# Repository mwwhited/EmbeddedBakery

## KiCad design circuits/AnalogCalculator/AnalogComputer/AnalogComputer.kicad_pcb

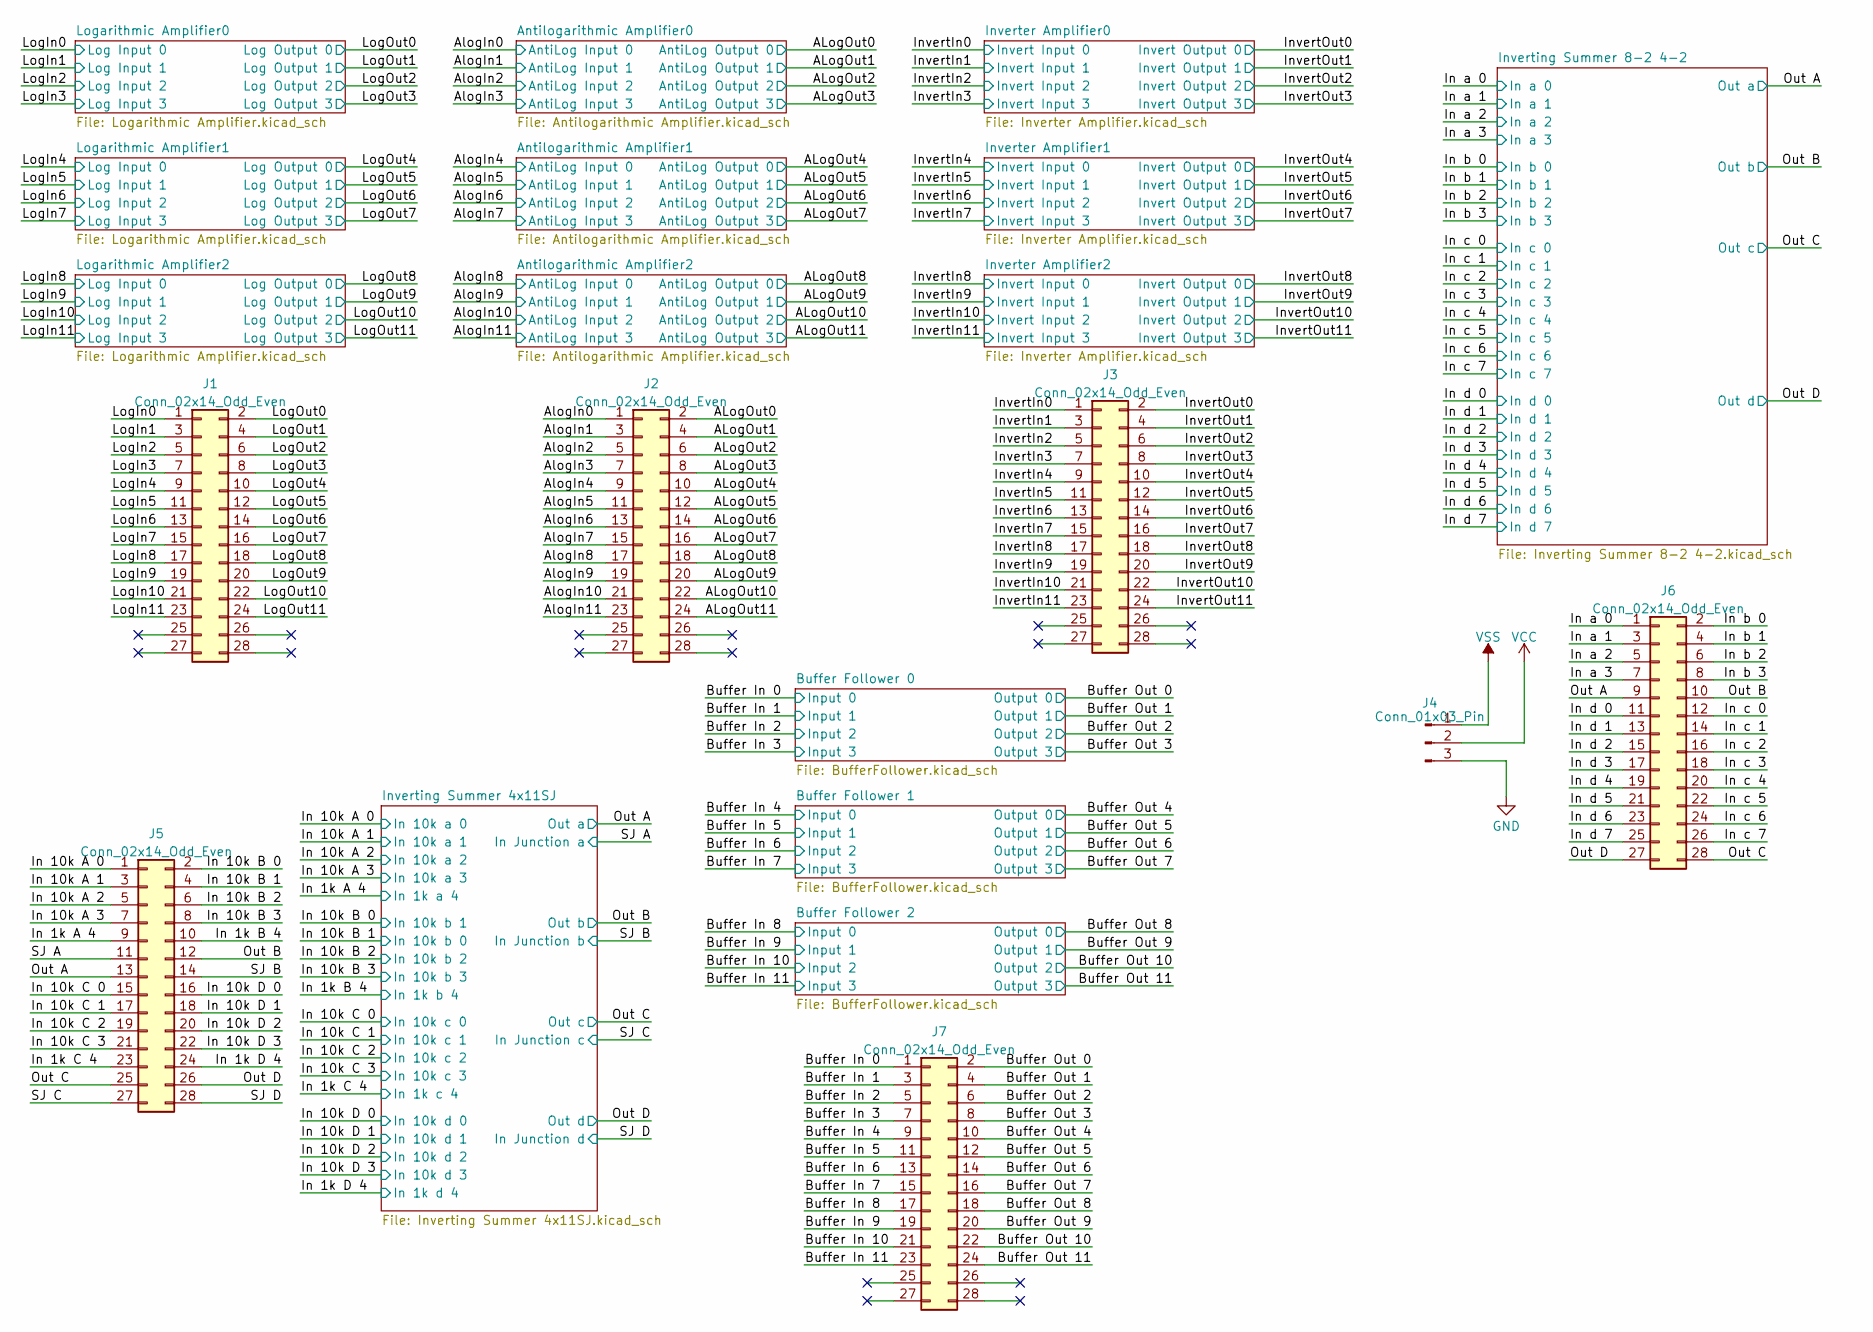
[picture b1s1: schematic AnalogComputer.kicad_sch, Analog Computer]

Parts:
J1, J2, J3, J5, J6, J7: Conn_02x14_Odd_Even; PinHeader_2x14_P2.54mm_Vertical
J4: Conn_01x03_Pin; JST_XH_B3B-XH-AM_1x03_P2.50mm_Vertical

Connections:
/ALogOut0: J2.2; also elsewhere on the board
/ALogOut1: J2.4; also elsewhere on the board
/ALogOut2: J2.6; also elsewhere on the board
/ALogOut3: J2.8; also elsewhere on the board
/ALogOut4: J2.10; also elsewhere on the board
/ALogOut5: J2.12; also elsewhere on the board
/ALogOut6: J2.14; also elsewhere on the board
/ALogOut7: J2.16; also elsewhere on the board
/ALogOut8: J2.18; also elsewhere on the board
/ALogOut9: J2.20; also elsewhere on the board
/ALogOut10: J2.22; also elsewhere on the board
/ALogOut11: J2.24; also elsewhere on the board
/AlogIn0: J2.1; also elsewhere on the board
/AlogIn1: J2.3; also elsewhere on the board
/AlogIn2: J2.5; also elsewhere on the board
/AlogIn3: J2.7; also elsewhere on the board
/AlogIn4: J2.9; also elsewhere on the board
/AlogIn5: J2.11; also elsewhere on the board
/AlogIn6: J2.13; also elsewhere on the board
/AlogIn7: J2.15; also elsewhere on the board
/AlogIn8: J2.17; also elsewhere on the board
/AlogIn9: J2.19; also elsewhere on the board
/AlogIn10: J2.21; also elsewhere on the board
/AlogIn11: J2.23; also elsewhere on the board
/Buffer In 0: J7.1; also elsewhere on the board
/Buffer In 1: J7.3; also elsewhere on the board
/Buffer In 2: J7.5; also elsewhere on the board
/Buffer In 3: J7.7; also elsewhere on the board
/Buffer In 4: J7.9; also elsewhere on the board
/Buffer In 5: J7.11; also elsewhere on the board
/Buffer In 6: J7.13; also elsewhere on the board
/Buffer In 7: J7.15; also elsewhere on the board
/Buffer In 8: J7.17; also elsewhere on the board
/Buffer In 9: J7.19; also elsewhere on the board
/Buffer In 10: J7.21; also elsewhere on the board
/Buffer In 11: J7.23; also elsewhere on the board
/Buffer Out 0: J7.2; also elsewhere on the board
/Buffer Out 1: J7.4; also elsewhere on the board
/Buffer Out 2: J7.6; also elsewhere on the board
/Buffer Out 3: J7.8; also elsewhere on the board
/Buffer Out 4: J7.10; also elsewhere on the board
/Buffer Out 5: J7.12; also elsewhere on the board
/Buffer Out 6: J7.14; also elsewhere on the board
/Buffer Out 7: J7.16; also elsewhere on the board
/Buffer Out 8: J7.18; also elsewhere on the board
/Buffer Out 9: J7.20; also elsewhere on the board
/Buffer Out 10: J7.22; also elsewhere on the board
/Buffer Out 11: J7.24; also elsewhere on the board
/In 1k A 4: J5.9; also elsewhere on the board
/In 1k B 4: J5.10; also elsewhere on the board
/In 1k C 4: J5.23; also elsewhere on the board
/In 1k D 4: J5.24; also elsewhere on the board
/In 10k A 0: J5.1; also elsewhere on the board
/In 10k A 1: J5.3; also elsewhere on the board
/In 10k A 2: J5.5; also elsewhere on the board
/In 10k A 3: J5.7; also elsewhere on the board
/In 10k B 0: J5.2; also elsewhere on the board
/In 10k B 1: J5.4; also elsewhere on the board
/In 10k B 2: J5.6; also elsewhere on the board
/In 10k B 3: J5.8; also elsewhere on the board
/In 10k C 0: J5.15; also elsewhere on the board
/In 10k C 1: J5.17; also elsewhere on the board
/In 10k C 2: J5.19; also elsewhere on the board
/In 10k C 3: J5.21; also elsewhere on the board
/In 10k D 0: J5.16; also elsewhere on the board
/In 10k D 1: J5.18; also elsewhere on the board
/In 10k D 2: J5.20; also elsewhere on the board
/In 10k D 3: J5.22; also elsewhere on the board
/In a 0: J6.1; also elsewhere on the board
/In a 1: J6.3; also elsewhere on the board
/In a 2: J6.5; also elsewhere on the board
/In a 3: J6.7; also elsewhere on the board
/In b 0: J6.2; also elsewhere on the board
/In b 1: J6.4; also elsewhere on the board
/In b 2: J6.6; also elsewhere on the board
/In b 3: J6.8; also elsewhere on the board
/In c 0: J6.12; also elsewhere on the board
/In c 1: J6.14; also elsewhere on the board
/In c 2: J6.16; also elsewhere on the board
/In c 3: J6.18; also elsewhere on the board
/In c 4: J6.20; also elsewhere on the board
/In c 5: J6.22; also elsewhere on the board
/In c 6: J6.24; also elsewhere on the board
/In c 7: J6.26; also elsewhere on the board
/In d 0: J6.11; also elsewhere on the board
/In d 1: J6.13; also elsewhere on the board
/In d 2: J6.15; also elsewhere on the board
/In d 3: J6.17; also elsewhere on the board
/In d 4: J6.19; also elsewhere on the board
/In d 5: J6.21; also elsewhere on the board
/In d 6: J6.23; also elsewhere on the board
/In d 7: J6.25; also elsewhere on the board
/InvertIn0: J3.1; also elsewhere on the board
/InvertIn1: J3.3; also elsewhere on the board
/InvertIn2: J3.5; also elsewhere on the board
/InvertIn3: J3.7; also elsewhere on the board
/InvertIn4: J3.9; also elsewhere on the board
/InvertIn5: J3.11; also elsewhere on the board
/InvertIn6: J3.13; also elsewhere on the board
/InvertIn7: J3.15; also elsewhere on the board
/InvertIn8: J3.17; also elsewhere on the board
/InvertIn9: J3.19; also elsewhere on the board
/InvertIn10: J3.21; also elsewhere on the board
/InvertIn11: J3.23; also elsewhere on the board
/InvertOut4: J3.10; also elsewhere on the board
/InvertOut5: J3.12; also elsewhere on the board
/InvertOut6: J3.14; also elsewhere on the board
/InvertOut7: J3.16; also elsewhere on the board
/InvertOut8: J3.18; also elsewhere on the board
/InvertOut9: J3.20; also elsewhere on the board
/InvertOut10: J3.22; also elsewhere on the board
/InvertOut11: J3.24; also elsewhere on the board
/LogIn0: J1.1; also elsewhere on the board
/LogIn1: J1.3; also elsewhere on the board
/LogIn2: J1.5; also elsewhere on the board
/LogIn3: J1.7; also elsewhere on the board
/LogIn4: J1.9; also elsewhere on the board
/LogIn5: J1.11; also elsewhere on the board
/LogIn6: J1.13; also elsewhere on the board
/LogIn7: J1.15; also elsewhere on the board
/LogIn8: J1.17; also elsewhere on the board
/LogIn9: J1.19; also elsewhere on the board
/LogIn10: J1.21; also elsewhere on the board
/LogIn11: J1.23; also elsewhere on the board
/LogOut0: J1.2; also elsewhere on the board
/LogOut1: J1.4; also elsewhere on the board
/LogOut2: J1.6; also elsewhere on the board
/LogOut3: J1.8; also elsewhere on the board
/LogOut4: J1.10; also elsewhere on the board
/LogOut5: J1.12; also elsewhere on the board
/LogOut6: J1.14; also elsewhere on the board
/LogOut7: J1.16; also elsewhere on the board
/LogOut8: J1.18; also elsewhere on the board
/LogOut9: J1.20; also elsewhere on the board
/LogOut10: J1.22; also elsewhere on the board
/LogOut11: J1.24; also elsewhere on the board
/Out A: J6.9; also elsewhere on the board
/Out B: J6.10; also elsewhere on the board
/Out C: J6.28; also elsewhere on the board
/Out D: J6.27; also elsewhere on the board
/Out A: J5.13; also elsewhere on the board
/Out B: J5.12; also elsewhere on the board
/Out C: J5.25; also elsewhere on the board
/Out D: J5.26; also elsewhere on the board
/SJ A: J5.11; also elsewhere on the board
/SJ B: J5.14; also elsewhere on the board
/SJ C: J5.27; also elsewhere on the board
/SJ D: J5.28; also elsewhere on the board
GND: J4.3; also elsewhere on the board
VCC: J4.2; also elsewhere on the board
VSS: J4.1; also elsewhere on the board

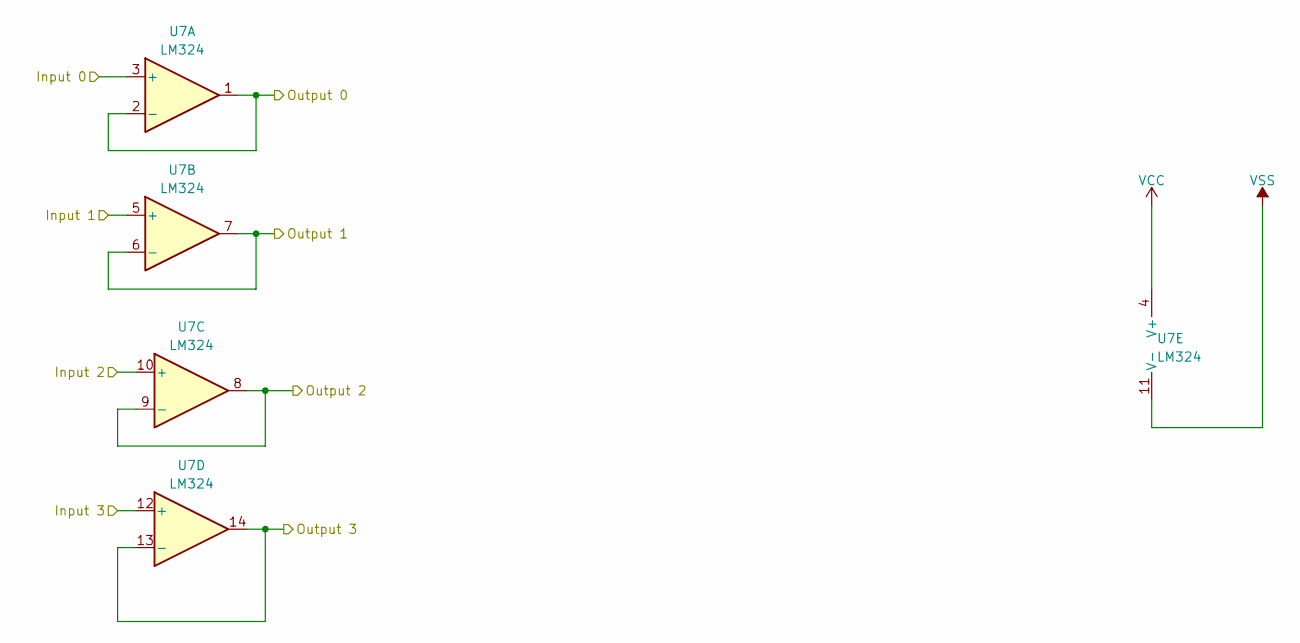
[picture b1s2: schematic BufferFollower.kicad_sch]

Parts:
U7: LM324; DIP-14_W7.62mm_Socket

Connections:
GND: U7.3 (+), U7.5 (+), U7.10 (+), U7.12 (+); also elsewhere on the board
VCC: U7.4 (V+); also elsewhere on the board
VSS: U7.11 (V-); also elsewhere on the board

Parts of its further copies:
U8, U9, U12, U13, U14: LM324; DIP-14_W7.62mm_Socket

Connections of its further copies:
/Buffer In 0: U12.3 (+); also elsewhere on the board
/Buffer In 1: U12.5 (+); also elsewhere on the board
/Buffer In 2: U12.10 (+); also elsewhere on the board
/Buffer In 3: U12.12 (+); also elsewhere on the board
/Buffer In 4: U13.3 (+); also elsewhere on the board
/Buffer In 5: U13.5 (+); also elsewhere on the board
/Buffer In 6: U13.10 (+); also elsewhere on the board
/Buffer In 7: U13.12 (+); also elsewhere on the board
/Buffer In 8: U14.3 (+); also elsewhere on the board
/Buffer In 9: U14.5 (+); also elsewhere on the board
/Buffer In 10: U14.10 (+); also elsewhere on the board
/Buffer In 11: U14.12 (+); also elsewhere on the board
/Buffer Out 0: U12.1, U12.2 (-); also elsewhere on the board
/Buffer Out 1: U12.6 (-), U12.7; also elsewhere on the board
/Buffer Out 2: U12.8, U12.9 (-); also elsewhere on the board
/Buffer Out 3: U12.13 (-), U12.14; also elsewhere on the board
/Buffer Out 4: U13.1, U13.2 (-); also elsewhere on the board
/Buffer Out 5: U13.6 (-), U13.7; also elsewhere on the board
/Buffer Out 6: U13.8, U13.9 (-); also elsewhere on the board
/Buffer Out 7: U13.13 (-), U13.14; also elsewhere on the board
/Buffer Out 8: U14.1, U14.2 (-); also elsewhere on the board
/Buffer Out 9: U14.6 (-), U14.7; also elsewhere on the board
/Buffer Out 10: U14.8, U14.9 (-); also elsewhere on the board
/Buffer Out 11: U14.13 (-), U14.14; also elsewhere on the board
/InvertOut4: U8.1; also elsewhere on the board
/InvertOut5: U8.7; also elsewhere on the board
/InvertOut6: U8.8; also elsewhere on the board
/InvertOut7: U8.14; also elsewhere on the board
/InvertOut8: U9.1; also elsewhere on the board
/InvertOut9: U9.7; also elsewhere on the board
/InvertOut10: U9.8; also elsewhere on the board
/InvertOut11: U9.14; also elsewhere on the board
GND: U8.3 (+), U8.5 (+), U8.10 (+), U8.12 (+), U9.3 (+), U9.5 (+), U9.10 (+), U9.12 (+); also elsewhere on the board
unnamed 177: U8.2 (-); also elsewhere on the board
unnamed 178: U8.6 (-); also elsewhere on the board
unnamed 179: U8.9 (-); also elsewhere on the board
unnamed 180: U8.13 (-); also elsewhere on the board
unnamed 181: U9.2 (-); also elsewhere on the board
unnamed 182: U9.6 (-); also elsewhere on the board
unnamed 183: U9.9 (-); also elsewhere on the board
unnamed 184: U9.13 (-); also elsewhere on the board
VCC: U8.4 (V+), U9.4 (V+), U12.4 (V+), U13.4 (V+), U14.4 (V+); also elsewhere on the board
VSS: U8.11 (V-), U9.11 (V-), U12.11 (V-), U13.11 (V-), U14.11 (V-); also elsewhere on the board

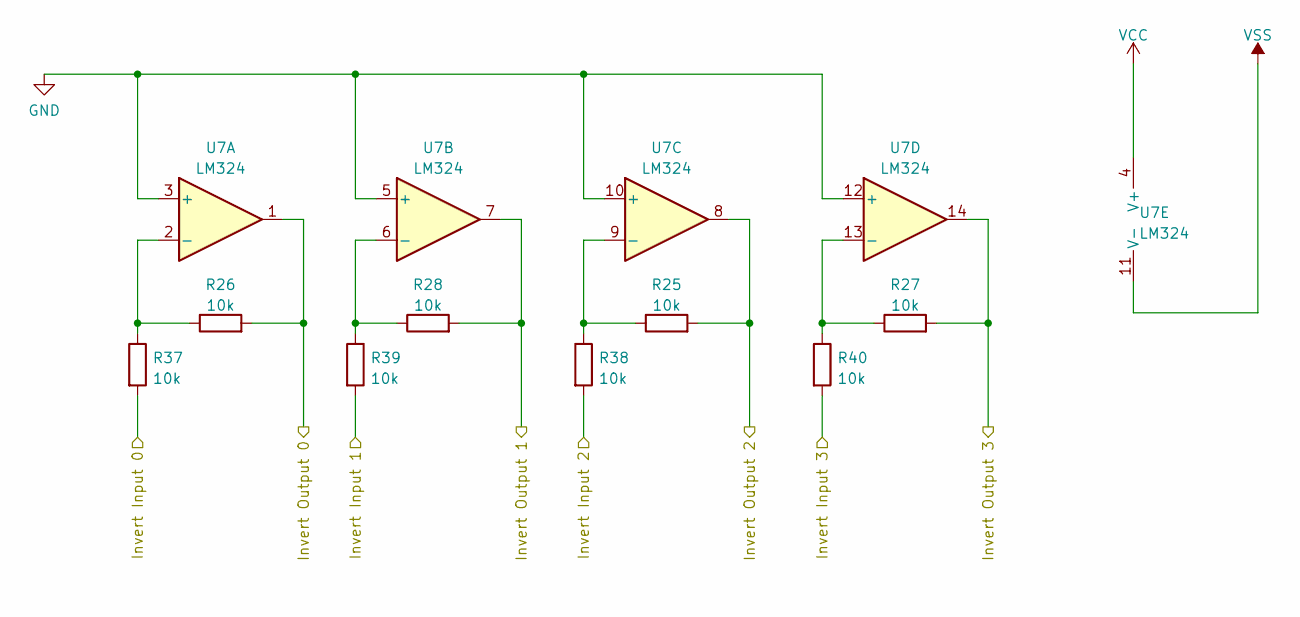
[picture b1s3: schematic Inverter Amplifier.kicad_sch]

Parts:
R25, R26, R27, R28, R37, R38, R39, R40: 10k; R_Axial_DIN0204_L3.6mm_D1.6mm_P2.54mm_Vertical
U7: LM324; DIP-14_W7.62mm_Socket

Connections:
/InvertIn0: R37.2; also elsewhere on the board
/InvertIn1: R39.2; also elsewhere on the board
/InvertIn2: R38.2; also elsewhere on the board
/InvertIn3: R40.2; also elsewhere on the board
GND: U7.3 (+), U7.5 (+), U7.10 (+), U7.12 (+); also elsewhere on the board
VCC: U7.4 (V+); also elsewhere on the board
VSS: U7.11 (V-); also elsewhere on the board

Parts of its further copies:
R29, R30, R31, R32, R33, R34, R35, R36, R41, R42, R43, R44, R45, R46, R47, R48: 10k; R_Axial_DIN0204_L3.6mm_D1.6mm_P2.54mm_Vertical
U8, U9: LM324; DIP-14_W7.62mm_Socket

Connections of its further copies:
/InvertIn4: R45.2; also elsewhere on the board
/InvertIn5: R44.2; also elsewhere on the board
/InvertIn6: R43.2; also elsewhere on the board
/InvertIn7: R41.2; also elsewhere on the board
/InvertIn8: R47.2; also elsewhere on the board
/InvertIn9: R48.2; also elsewhere on the board
/InvertIn10: R46.2; also elsewhere on the board
/InvertIn11: R42.2; also elsewhere on the board
/InvertOut4: R30.2, U8.1; also elsewhere on the board
/InvertOut5: R32.2, U8.7; also elsewhere on the board
/InvertOut6: R33.2, U8.8; also elsewhere on the board
/InvertOut7: R34.2, U8.14; also elsewhere on the board
/InvertOut8: R31.2, U9.1; also elsewhere on the board
/InvertOut9: R29.2, U9.7; also elsewhere on the board
/InvertOut10: R35.2, U9.8; also elsewhere on the board
/InvertOut11: R36.2, U9.14; also elsewhere on the board
GND: U8.3 (+), U8.5 (+), U8.10 (+), U8.12 (+), U9.3 (+), U9.5 (+), U9.10 (+), U9.12 (+); also elsewhere on the board
unnamed: R30.1, R45.1, U8.2 (-)
unnamed: R32.1, R44.1, U8.6 (-)
unnamed: R33.1, R43.1, U8.9 (-)
unnamed: R34.1, R41.1, U8.13 (-)
unnamed: R31.1, R47.1, U9.2 (-)
unnamed: R29.1, R48.1, U9.6 (-)
unnamed: R35.1, R46.1, U9.9 (-)
unnamed: R36.1, R42.1, U9.13 (-)
VCC: U8.4 (V+), U9.4 (V+); also elsewhere on the board
VSS: U8.11 (V-), U9.11 (V-); also elsewhere on the board

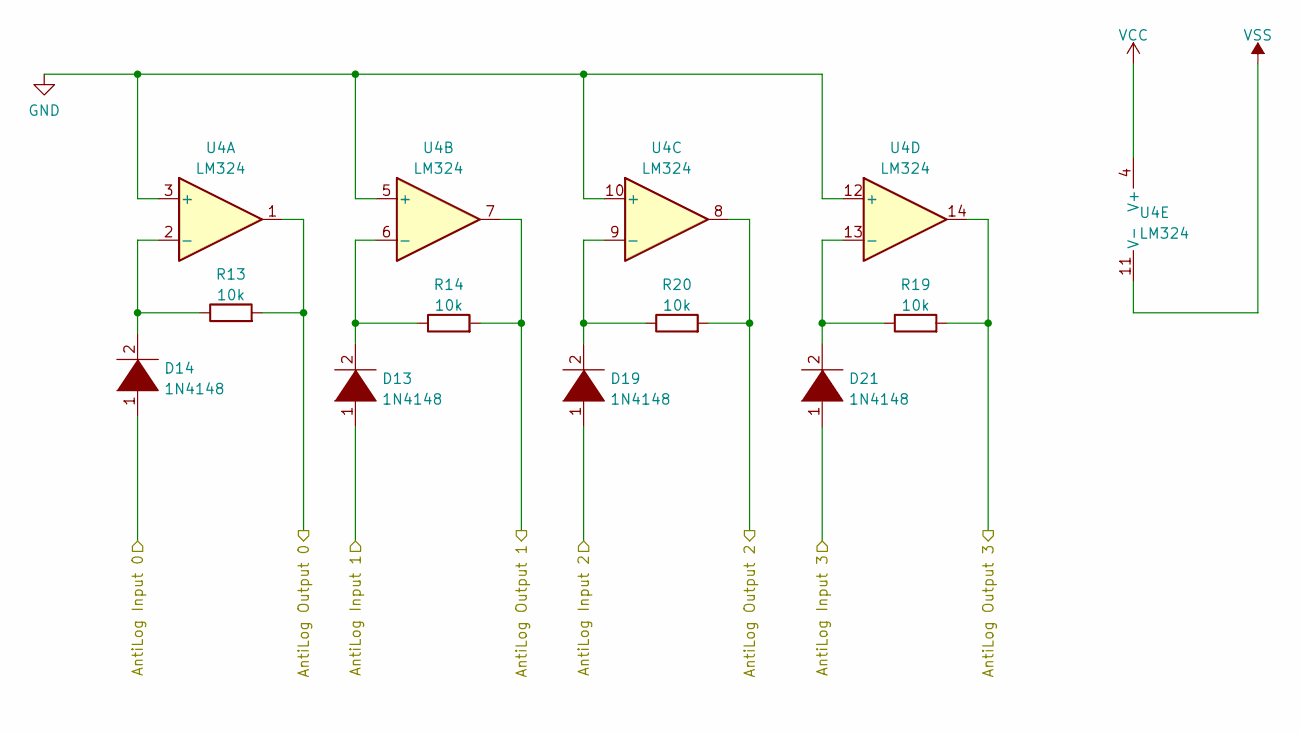
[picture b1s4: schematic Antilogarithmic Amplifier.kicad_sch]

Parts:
D13, D14, D19, D21: 1N4148; D_A-405_P2.54mm_Vertical_AnodeUp
R13, R14, R19, R20: 10k; R_Axial_DIN0204_L3.6mm_D1.6mm_P2.54mm_Vertical
U4: LM324; DIP-14_W7.62mm_Socket

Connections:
/ALogOut0: R13.2, U4.1; also elsewhere on the board
/ALogOut1: R14.2, U4.7; also elsewhere on the board
/ALogOut2: R20.2, U4.8; also elsewhere on the board
/ALogOut3: R19.2, U4.14; also elsewhere on the board
/AlogIn0: D14.1 (K); also elsewhere on the board
/AlogIn1: D13.1 (K); also elsewhere on the board
/AlogIn2: D19.1 (K); also elsewhere on the board
/AlogIn3: D21.1 (K); also elsewhere on the board
GND: U4.3 (+), U4.5 (+), U4.10 (+), U4.12 (+); also elsewhere on the board
unnamed: D13.2 (A), R14.1, U4.6 (-)
unnamed: D14.2 (A), R13.1, U4.2 (-)
unnamed: D19.2 (A), R20.1, U4.9 (-)
unnamed: D21.2 (A), R19.1, U4.13 (-)
VCC: U4.4 (V+); also elsewhere on the board
VSS: U4.11 (V-); also elsewhere on the board

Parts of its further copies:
D15, D16, D17, D18, D20, D22, D23, D24: 1N4148; D_A-405_P2.54mm_Vertical_AnodeUp
R15, R16, R17, R18, R21, R22, R23, R24: 10k; R_Axial_DIN0204_L3.6mm_D1.6mm_P2.54mm_Vertical
U5, U6: LM324; DIP-14_W7.62mm_Socket

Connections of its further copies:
/ALogOut4: R18.2, U6.1; also elsewhere on the board
/ALogOut5: R17.2, U6.7; also elsewhere on the board
/ALogOut6: R24.2, U6.8; also elsewhere on the board
/ALogOut7: R23.2, U6.14; also elsewhere on the board
/ALogOut8: R16.2, U5.1; also elsewhere on the board
/ALogOut9: R15.2, U5.7; also elsewhere on the board
/ALogOut10: R21.2, U5.8; also elsewhere on the board
/ALogOut11: R22.2, U5.14; also elsewhere on the board
/AlogIn4: D17.1 (K); also elsewhere on the board
/AlogIn5: D18.1 (K); also elsewhere on the board
/AlogIn6: D24.1 (K); also elsewhere on the board
/AlogIn7: D23.1 (K); also elsewhere on the board
/AlogIn8: D16.1 (K); also elsewhere on the board
/AlogIn9: D15.1 (K); also elsewhere on the board
/AlogIn10: D22.1 (K); also elsewhere on the board
/AlogIn11: D20.1 (K); also elsewhere on the board
GND: U5.3 (+), U5.5 (+), U5.10 (+), U5.12 (+), U6.3 (+), U6.5 (+), U6.10 (+), U6.12 (+); also elsewhere on the board
unnamed: D15.2 (A), R15.1, U5.6 (-)
unnamed: D16.2 (A), R16.1, U5.2 (-)
unnamed: D17.2 (A), R18.1, U6.2 (-)
unnamed: D18.2 (A), R17.1, U6.6 (-)
unnamed: D20.2 (A), R22.1, U5.13 (-)
unnamed: D22.2 (A), R21.1, U5.9 (-)
unnamed: D23.2 (A), R23.1, U6.13 (-)
unnamed: D24.2 (A), R24.1, U6.9 (-)
VCC: U5.4 (V+), U6.4 (V+); also elsewhere on the board
VSS: U5.11 (V-), U6.11 (V-); also elsewhere on the board

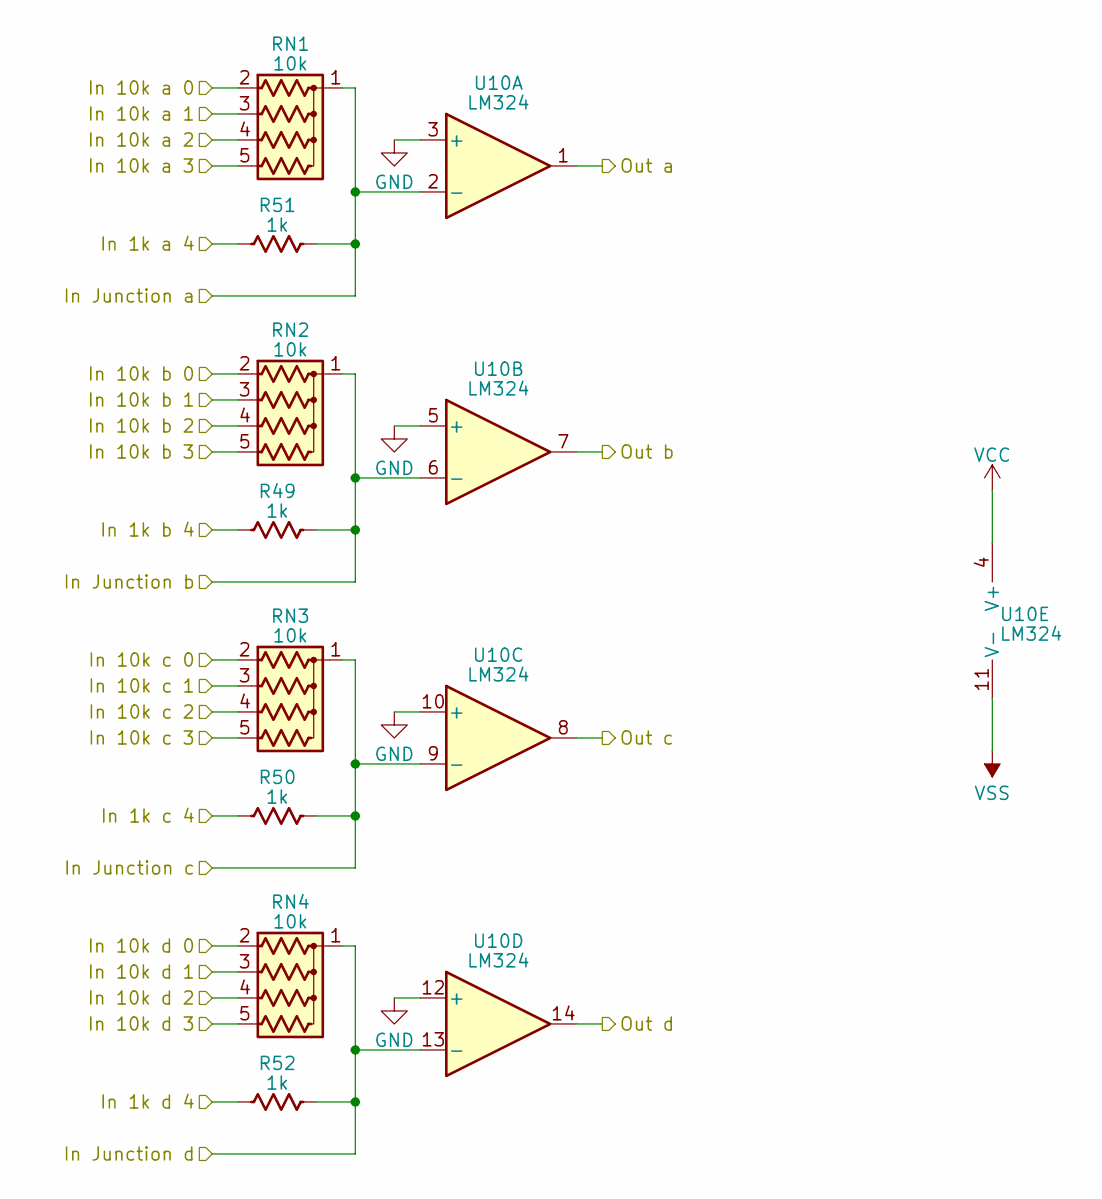
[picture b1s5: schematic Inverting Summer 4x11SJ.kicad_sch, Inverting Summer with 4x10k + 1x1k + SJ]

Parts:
R49, R50, R51, R52: 1k; R_Axial_DIN0204_L3.6mm_D1.6mm_P2.54mm_Vertical
RN1, RN2, RN3, RN4: 10k; R_Array_SIP5
U10: LM324; DIP-14_W7.62mm_Socket

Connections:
/In 1k A 4: R51.1; also elsewhere on the board
/In 1k B 4: R49.1; also elsewhere on the board
/In 1k C 4: R50.1; also elsewhere on the board
/In 1k D 4: R52.1; also elsewhere on the board
/In 10k A 0: RN1.2 (R1); also elsewhere on the board
/In 10k A 1: RN1.3 (R2); also elsewhere on the board
/In 10k A 2: RN1.4 (R3); also elsewhere on the board
/In 10k A 3: RN1.5 (R4); also elsewhere on the board
/In 10k B 0: RN2.3 (R2); also elsewhere on the board
/In 10k B 1: RN2.2 (R1); also elsewhere on the board
/In 10k B 2: RN2.4 (R3); also elsewhere on the board
/In 10k B 3: RN2.5 (R4); also elsewhere on the board
/In 10k C 0: RN3.2 (R1); also elsewhere on the board
/In 10k C 1: RN3.3 (R2); also elsewhere on the board
/In 10k C 2: RN3.4 (R3); also elsewhere on the board
/In 10k C 3: RN3.5 (R4); also elsewhere on the board
/In 10k D 0: RN4.2 (R1); also elsewhere on the board
/In 10k D 1: RN4.3 (R2); also elsewhere on the board
/In 10k D 2: RN4.4 (R3); also elsewhere on the board
/In 10k D 3: RN4.5 (R4); also elsewhere on the board
/Out A: U10.1; also elsewhere on the board
/Out B: U10.7; also elsewhere on the board
/Out C: U10.8; also elsewhere on the board
/Out D: U10.14; also elsewhere on the board
/SJ A: R51.2, RN1.1 (common), U10.2 (-); also elsewhere on the board
/SJ B: R49.2, RN2.1 (common), U10.6 (-); also elsewhere on the board
/SJ C: R50.2, RN3.1 (common), U10.9 (-); also elsewhere on the board
/SJ D: R52.2, RN4.1 (common), U10.13 (-); also elsewhere on the board
GND: U10.3 (+), U10.5 (+), U10.10 (+), U10.12 (+); also elsewhere on the board
VCC: U10.4 (V+); also elsewhere on the board
VSS: U10.11 (V-); also elsewhere on the board

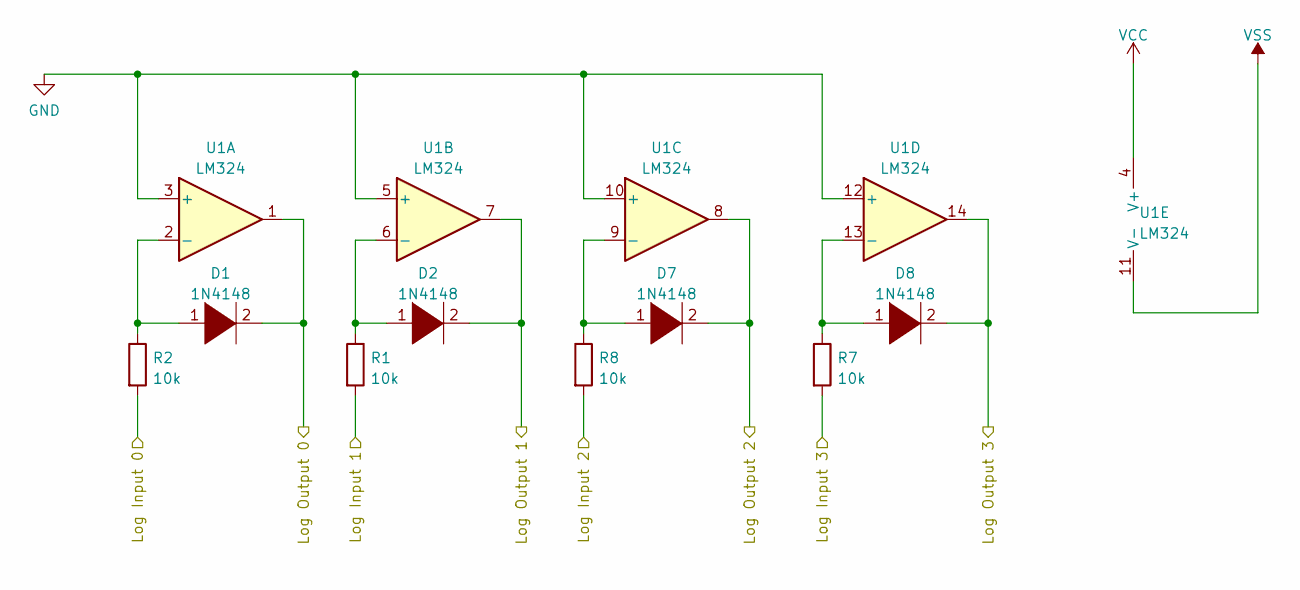
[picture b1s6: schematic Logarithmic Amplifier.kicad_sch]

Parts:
D1, D2, D7, D8: 1N4148; D_A-405_P2.54mm_Vertical_KathodeUp
R1, R2, R7, R8: 10k; R_Axial_DIN0204_L3.6mm_D1.6mm_P2.54mm_Vertical
U1: LM324; DIP-14_W7.62mm_Socket

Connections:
/LogIn0: R2.2; also elsewhere on the board
/LogIn1: R1.2; also elsewhere on the board
/LogIn2: R8.2; also elsewhere on the board
/LogIn3: R7.2; also elsewhere on the board
/LogOut0: D1.2 (A), U1.1; also elsewhere on the board
/LogOut1: D2.2 (A), U1.7; also elsewhere on the board
/LogOut2: D7.2 (A), U1.8; also elsewhere on the board
/LogOut3: D8.2 (A), U1.14; also elsewhere on the board
GND: U1.3 (+), U1.5 (+), U1.10 (+), U1.12 (+); also elsewhere on the board
unnamed: D1.1 (K), R2.1, U1.2 (-)
unnamed: D2.1 (K), R1.1, U1.6 (-)
unnamed: D7.1 (K), R8.1, U1.9 (-)
unnamed: D8.1 (K), R7.1, U1.13 (-)
VCC: U1.4 (V+); also elsewhere on the board
VSS: U1.11 (V-); also elsewhere on the board

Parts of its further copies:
D3, D4, D5, D6, D9, D10, D11, D12: 1N4148; D_A-405_P2.54mm_Vertical_KathodeUp
R3, R4, R5, R6, R9, R10, R11, R12: 10k; R_Axial_DIN0204_L3.6mm_D1.6mm_P2.54mm_Vertical
U2, U3: LM324; DIP-14_W7.62mm_Socket

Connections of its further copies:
/LogIn4: R6.2; also elsewhere on the board
/LogIn5: R5.2; also elsewhere on the board
/LogIn6: R12.2; also elsewhere on the board
/LogIn7: R11.2; also elsewhere on the board
/LogIn8: R4.2; also elsewhere on the board
/LogIn9: R3.2; also elsewhere on the board
/LogIn10: R9.2; also elsewhere on the board
/LogIn11: R10.2; also elsewhere on the board
/LogOut4: D6.2 (A), U3.1; also elsewhere on the board
/LogOut5: D5.2 (A), U3.7; also elsewhere on the board
/LogOut6: D12.2 (A), U3.8; also elsewhere on the board
/LogOut7: D11.2 (A), U3.14; also elsewhere on the board
/LogOut8: D3.2 (A), U2.1; also elsewhere on the board
/LogOut9: D4.2 (A), U2.7; also elsewhere on the board
/LogOut10: D10.2 (A), U2.8; also elsewhere on the board
/LogOut11: D9.2 (A), U2.14; also elsewhere on the board
GND: U2.3 (+), U2.5 (+), U2.10 (+), U2.12 (+), U3.3 (+), U3.5 (+), U3.10 (+), U3.12 (+); also elsewhere on the board
unnamed: D3.1 (K), R4.1, U2.2 (-)
unnamed: D4.1 (K), R3.1, U2.6 (-)
unnamed: D5.1 (K), R5.1, U3.6 (-)
unnamed: D6.1 (K), R6.1, U3.2 (-)
unnamed: D9.1 (K), R10.1, U2.13 (-)
unnamed: D10.1 (K), R9.1, U2.9 (-)
unnamed: D11.1 (K), R11.1, U3.13 (-)
unnamed: D12.1 (K), R12.1, U3.9 (-)
VCC: U2.4 (V+), U3.4 (V+); also elsewhere on the board
VSS: U2.11 (V-), U3.11 (V-); also elsewhere on the board

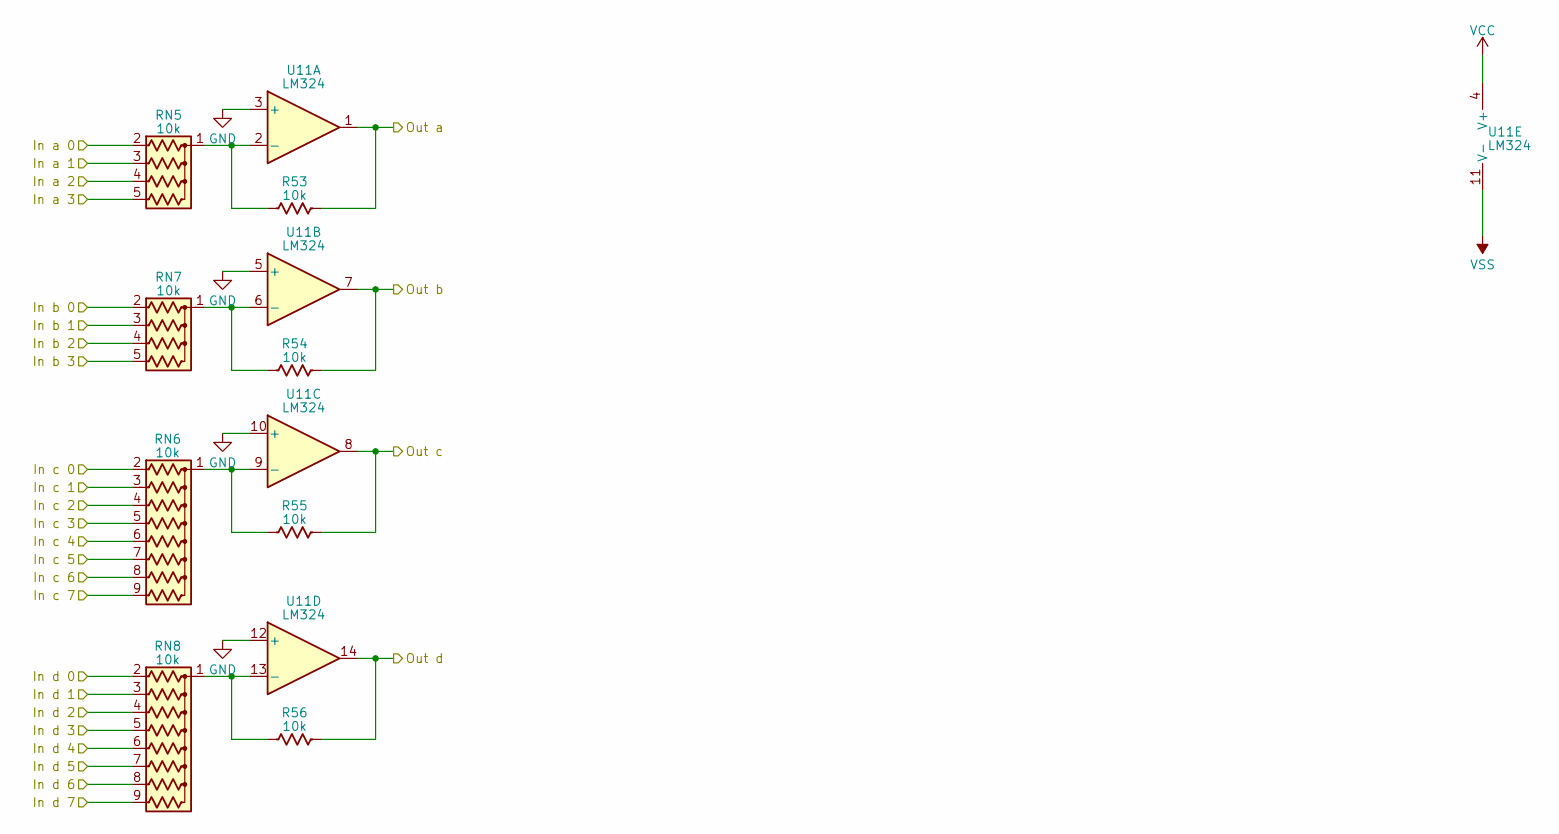
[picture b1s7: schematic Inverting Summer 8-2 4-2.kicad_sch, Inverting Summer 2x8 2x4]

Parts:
R53, R54, R55, R56: 10k; R_Axial_DIN0204_L3.6mm_D1.6mm_P2.54mm_Vertical
RN5, RN7: 10k; R_Array_SIP5
RN6, RN8: 10k; R_Array_SIP9
U11: LM324; DIP-14_W7.62mm_Socket

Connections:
/In a 0: RN5.2 (R1); also elsewhere on the board
/In a 1: RN5.3 (R2); also elsewhere on the board
/In a 2: RN5.4 (R3); also elsewhere on the board
/In a 3: RN5.5 (R4); also elsewhere on the board
/In b 0: RN7.2 (R1); also elsewhere on the board
/In b 1: RN7.3 (R2); also elsewhere on the board
/In b 2: RN7.4 (R3); also elsewhere on the board
/In b 3: RN7.5 (R4); also elsewhere on the board
/In c 0: RN6.2 (R1); also elsewhere on the board
/In c 1: RN6.3 (R2); also elsewhere on the board
/In c 2: RN6.4 (R3); also elsewhere on the board
/In c 3: RN6.5 (R4); also elsewhere on the board
/In c 4: RN6.6 (R5); also elsewhere on the board
/In c 5: RN6.7 (R6); also elsewhere on the board
/In c 6: RN6.8 (R7); also elsewhere on the board
/In c 7: RN6.9 (R8); also elsewhere on the board
/In d 0: RN8.2 (R1); also elsewhere on the board
/In d 1: RN8.3 (R2); also elsewhere on the board
/In d 2: RN8.4 (R3); also elsewhere on the board
/In d 3: RN8.5 (R4); also elsewhere on the board
/In d 4: RN8.6 (R5); also elsewhere on the board
/In d 5: RN8.7 (R6); also elsewhere on the board
/In d 6: RN8.8 (R7); also elsewhere on the board
/In d 7: RN8.9 (R8); also elsewhere on the board
/Out A: R53.2, U11.1; also elsewhere on the board
/Out B: R54.2, U11.7; also elsewhere on the board
/Out C: R55.2, U11.8; also elsewhere on the board
/Out D: R56.2, U11.14; also elsewhere on the board
GND: U11.3 (+), U11.5 (+), U11.10 (+), U11.12 (+); also elsewhere on the board
unnamed: R53.1, RN5.1 (common), U11.2 (-)
unnamed: R55.1, RN6.1 (common), U11.9 (-)
unnamed: R54.1, RN7.1 (common), U11.6 (-)
unnamed: R56.1, RN8.1 (common), U11.13 (-)
VCC: U11.4 (V+); also elsewhere on the board
VSS: U11.11 (V-); also elsewhere on the board

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
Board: 2 copper layers, 109 parts (1 on the bottom side), 195 nets, no tracks yet.

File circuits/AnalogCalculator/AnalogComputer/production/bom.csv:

Designator,Footprint,Quantity,Value,LCSC Part #
"D1, D10, D11, D12, D2, D3, D4, D5, D6, D7, D8, D9",D_A-405_P2.54mm_Vertical_KathodeUp,12,1N4148,
"D13, D14, D15, D16, D17, D18, D19, D20, D21, D22, D23, D24",D_A-405_P2.54mm_Vertical_AnodeUp,12,1N4148,
"J1, J2, J3",PinHeader_2x14_P2.54mm_Vertical,3,Conn_02x14_Odd_Even,
J4,JST_XH_B3B-XH-AM_1x03_P2.50mm_Vertical,1,Conn_01x03_Pin,
"R1, R10, R11, R12, R13, R14, R15, R16, R17, R18, R19, R2, R20, R21, R22, R23, R24, R25, R26, R27, R28, R29, R3, R30, R31, R32, R33, R34, R35, R36, R37, R38, R39, R4, R40, R41, R42, R43, R44, R45, R46, R47, R48, R5, R6, R7, R8, R9",R_Axial_DIN0204_L3.6mm_D1.6mm_P2.54mm_Vertical,48,10k,
"U1, U2, U3, U4, U5, U6, U7, U8, U9",DIP-14_W7.62mm_Socket,9,LM324,
